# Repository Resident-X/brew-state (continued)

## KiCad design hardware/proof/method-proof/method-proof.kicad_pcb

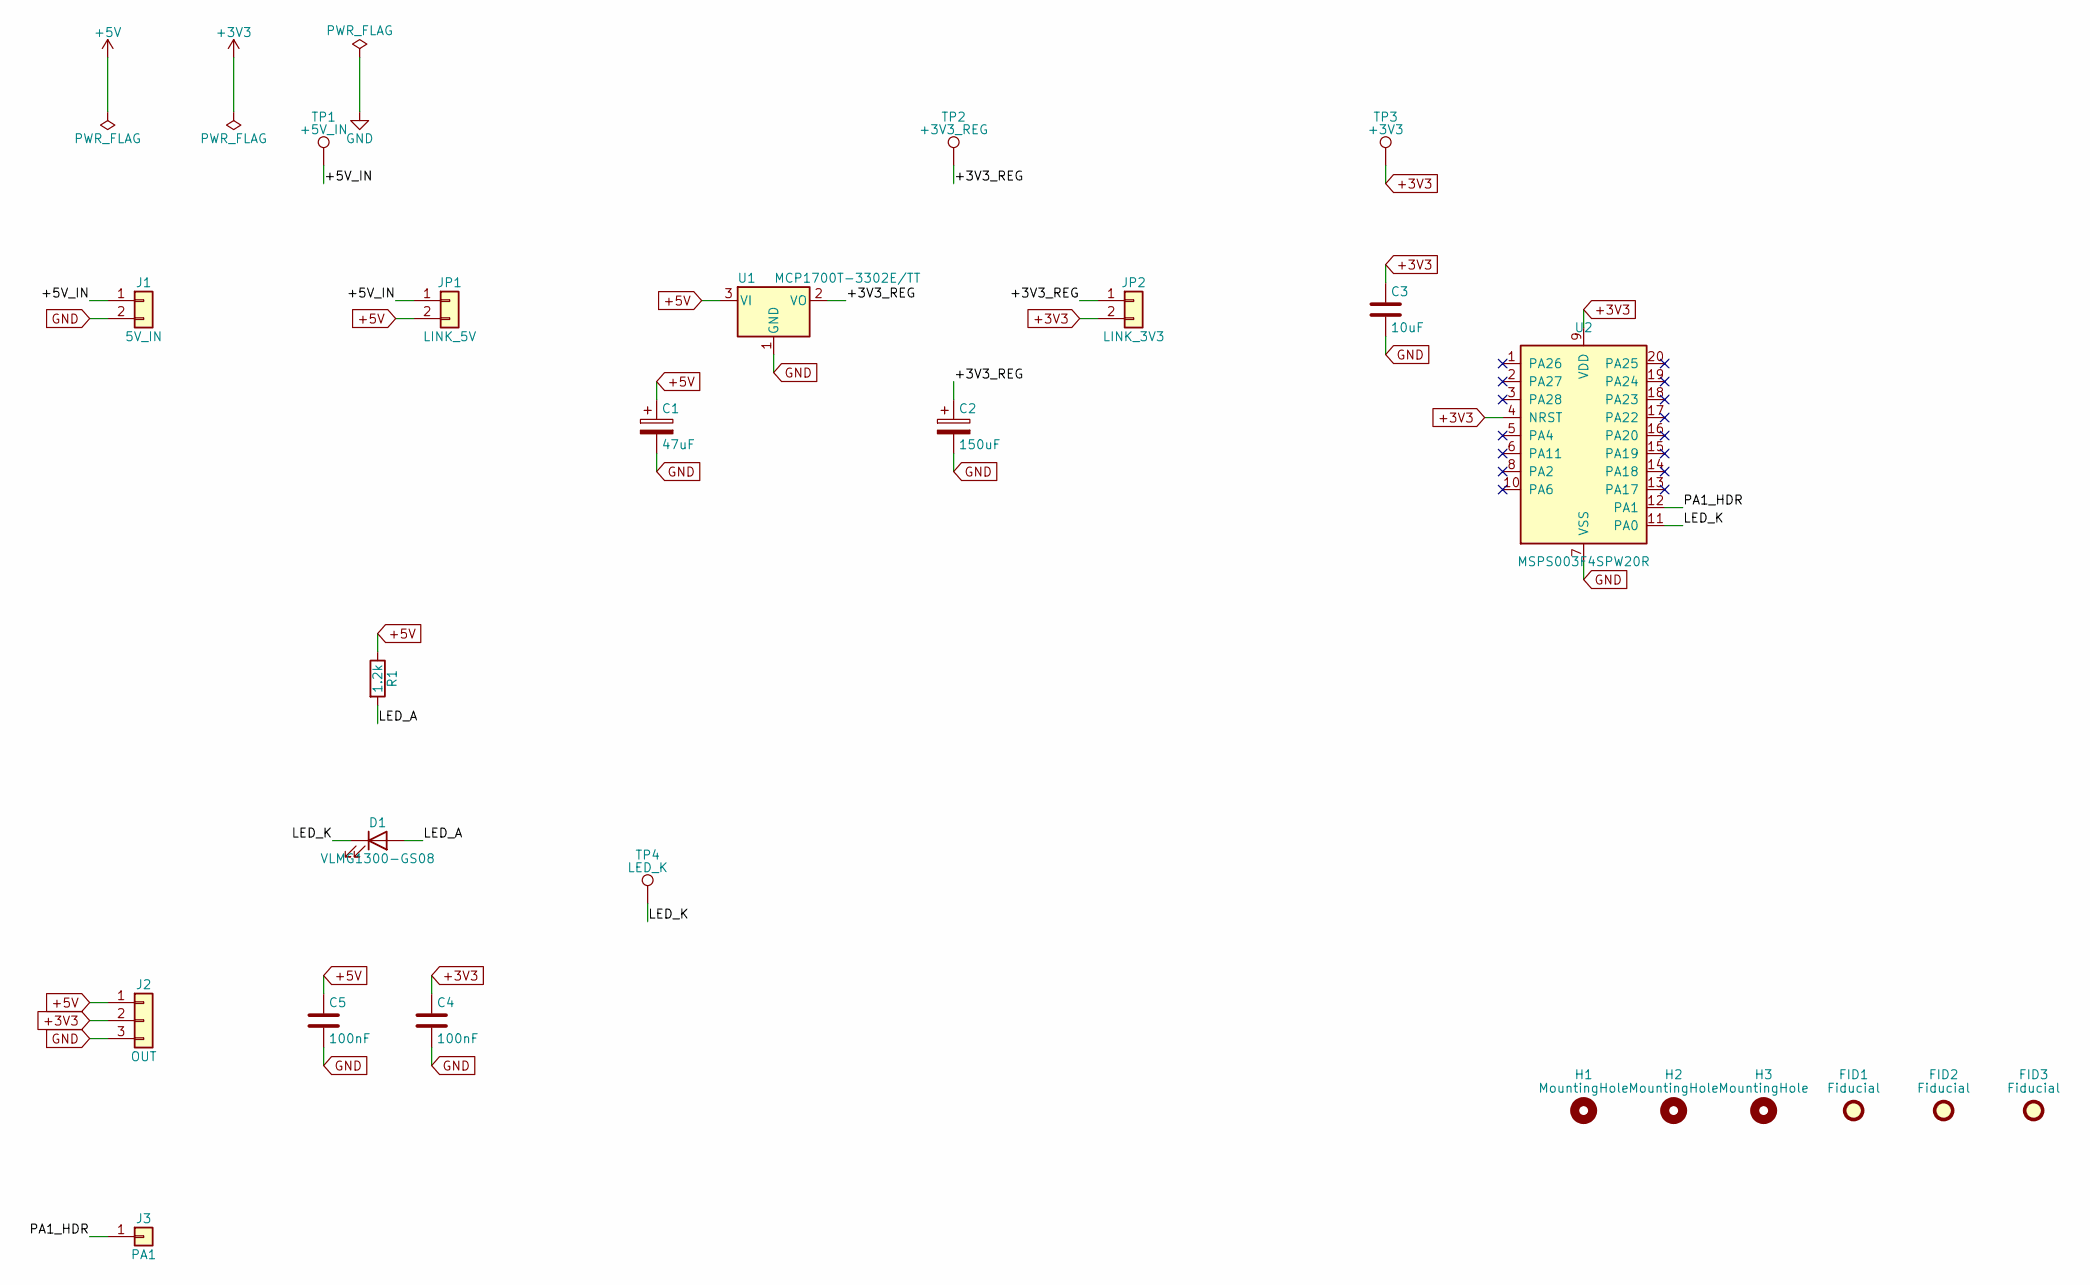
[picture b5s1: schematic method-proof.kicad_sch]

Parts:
C1: 47uF; CP_EIA-3528-21_Kemet-B; Rating 10V; MPN T520B476M010ATE035; LCSC C9100008
C2: 150uF; CP_EIA-3528-21_Kemet-B; Rating 6.3V; MPN T520B157M006ATE025; LCSC C9100014
C3: 10uF; C_0805_2012Metric; Rating 10V; MPN C0805C106K8RACTU; LCSC C9100009
C4, C5: 100nF; C_0603_1608Metric; Rating 16V; MPN C0603C104K4RACTU; LCSC C9100015
D1: VLMG1300-GS08; LED_0603_1608Metric; MPN VLMG1300-GS08; LCSC C9100011
FID1, FID2, FID3: Fiducial; Fiducial_1mm_Mask2mm; LCSC C9100016
H1, H2, H3: MountingHole; MountingHole_2.2mm_M2; LCSC C9100013
J1: 5V_IN; JST_XH_B2B-XH-A_1x02_P2.50mm_Vertical; Rating 3A; MPN B2B-XH-A(LF)(SN); LCSC C9100001
J2: OUT; JST_XH_B3B-XH-A_1x03_P2.50mm_Vertical; Rating 3A; MPN B3B-XH-A(LF)(SN); LCSC C9100002
J3: PA1; PinHeader_1x01_P2.54mm_Vertical; MPN TSW-101-07-T-S; LCSC C9100003
JP1: LINK_5V; PinHeader_1x02_P2.54mm_Vertical; MPN TSW-102-07-T-S; LCSC C9100004
JP2: LINK_3V3; PinHeader_1x02_P2.54mm_Vertical; MPN TSW-102-07-T-S; LCSC C9100005
R1: 1.2k; R_0603_1608Metric; Rating 0.1W; MPN CRCW06031K20FKEA; LCSC C9100010
TP1: +5V_IN; TestPoint_Pad_D1.0mm; LCSC C9100012
TP2: +3V3_REG; TestPoint_Pad_D1.0mm; LCSC C9100012
TP3: +3V3; TestPoint_Pad_D1.0mm; LCSC C9100012
TP4: LED_K; TestPoint_Pad_D1.0mm; LCSC C9100012
U1: MCP1700T-3302E/TT; SOT-23; MPN MCP1700T-3302E/TT; LCSC C9100006
U2: MSPS003F4SPW20R; TSSOP-20_4.4x6.5mm_P0.65mm; MPN MSPS003F4SPW20R; LCSC C9100007

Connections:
+3V3: C3.1, C4.1, J2.2, JP2.2, TP3.1 (1_1), U2.4 (NRST), U2.9 (VDD)
+5V: C1.1, C5.1, J2.1, JP1.2, R1.1, U1.3 (VI)
/+3V3_REG: C2.1, JP2.1, TP2.1 (1_1), U1.2 (VO)
/+5V_IN: J1.1, JP1.1, TP1.1 (1_1)
/LED_A: D1.2 (A), R1.2
/LED_K: D1.1 (K), TP4.1 (1_1), U2.11 (PA0)
/PA1_HDR: J3.1 (Pin_1_1), U2.12 (PA1)
GND: C1.2, C2.2, C3.2, C4.2, C5.2, J1.2, J2.3, U1.1 (GND), U2.7 (VSS)

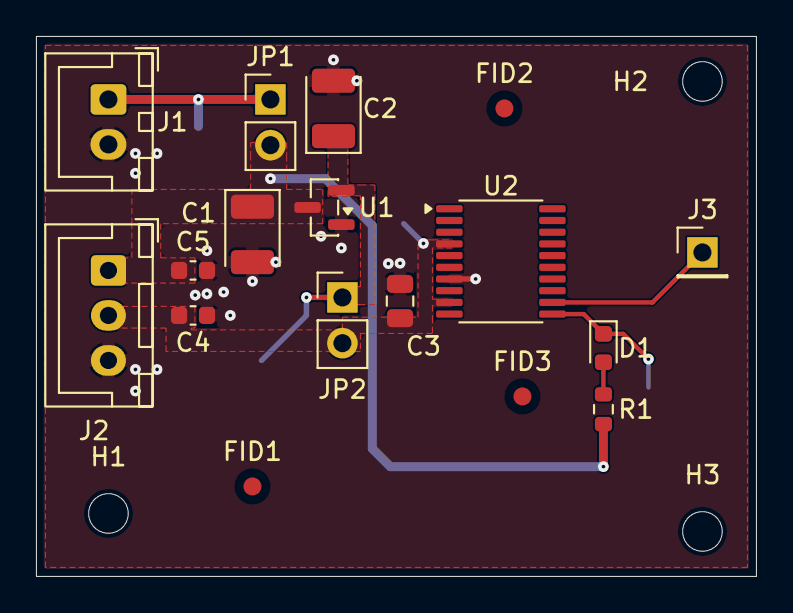
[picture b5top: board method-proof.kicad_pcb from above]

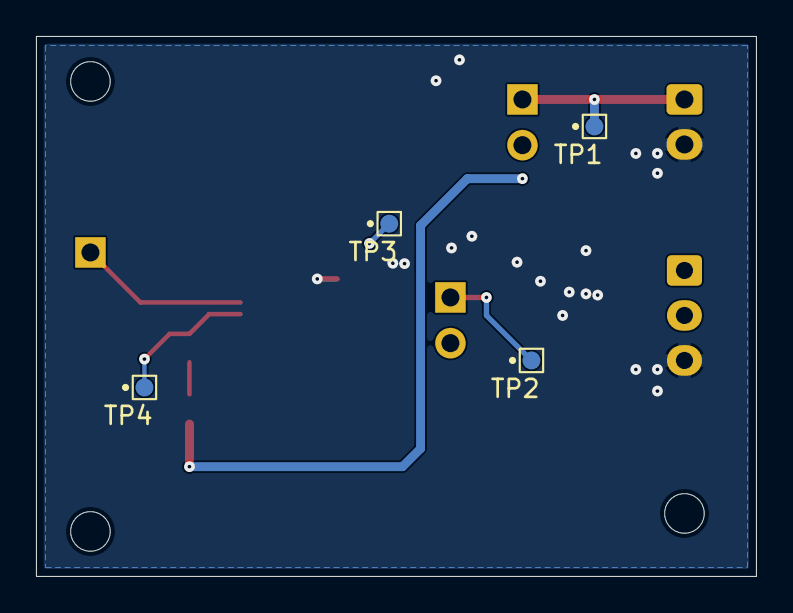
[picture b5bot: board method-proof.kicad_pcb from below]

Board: 4 copper layers, 40.0 x 30.0 mm, 24 parts (4 on the bottom side), 8 nets.

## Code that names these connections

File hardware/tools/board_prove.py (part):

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

def neutral_domain(extra: str, highest: str = "353.5533906"):
    """The mains neutral domain of the pin-limit record given `highest` as its figure and `extra` lines of keys."""
    return pin_limits(NEUTRAL_RAIL, f"    rail: MAINS_N\n    highest_voltage_v: {highest}\n{extra}")


def divider_over_its_rating(seed: Seed) -> None:
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
def riding_domain_on_a_host_below_the_floor(seed: Seed) -> None:
    """The line domain stated at 100 V and the neutral riding on it at half, which the record's derivation allows."""
    pin_limits(LINE_RAIL, "    rail: MAINS_L\n    highest_voltage_v: 100\n")(seed)
    neutral_domain("    rides_on: mains_line\n    fraction: 0.5\n", "50")(seed)


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

def mains_flag_on_lv_b(seed: Seed) -> None:
    """A schematic net class directive putting /LV_B, R2 pin 2's net, in Mains."""
    Q = sexpr.Quoted
    flag = ["netclass_flag", Q(""), ["length", "2.54"], ["shape", "round"], ["at", "45.72", "78.74", "0"],
            ["effects", ["font", ["size", "1.27", "1.27"]], ["justify", "left", "bottom"]],
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            if item[1] == "LV_B" and at[1:3] == ["63.5", "81.28"]:
                tree.remove(item)
                return
        raise AssertionError("the proof schematic has no LV_B label on R2 pin 2")
    seed.schematic(edit)


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

def pour_short_of_pad(seed: Seed) -> None:
    """/LV_A looping the long way round and ending 2.5 mm short of R2's pad 1, inside a pour of its net over the pad,
    which once left the pad out of the route-length rule's tree and the net unmeasured."""
    reroute("/LV_A", (LV_A_ENDS,), [(40, 10), (40, 6), (41, 5), (44, 5), (45, 6), (45, 7.5)])(seed)
    Q = sexpr.Quoted
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
def via_in_decoupling_path(seed: Seed) -> None:
    """U1's two pads typed as power inputs, a capacitor C9 across them 6 mm below U1, and a /LV_A via between C9's /LV_A pad
    and U1's /LV_A pin."""
    Q = sexpr.Quoted
    thru = ("thru_hole", ["*.Cu", "*.Mask"])
    part = small_part("C9", 43, 16, "0b0e5c1a-0000-4000-8000-000000000d00", ("1", *thru, "/LV_A", 0, 0, 1.2),
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def declared_record(first: str, second: str):
    head = "synthetic: true\ncontroller: none\nchannels:\n"
    entry = "  - channel: {label}\n    net: {net}\n    connector: J2\n    connector_pin: {pin}\n{extra}"
    return lambda seed: seed.write("pin-allocation.yaml", head + entry.format(label="lv_a", net="LV_A", pin=1, extra=first)
                                   + (entry.format(label="lv_b", net="LV_B", pin=2, extra=second) if second is not None else ""))


#: Where the far channel fault places its copy: a machine folder, which no proof design sits in, holding the copy alone.
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     "down to 0.9 mm, and the layout leaves 0.84 mm",
     both(TERMINAL_SHORTFALL, NET_PAIR_BANDS, exceptions(net_pair_entry("clearance", ("/MAINS_L",), 125, 0.9, ("/MAINS_N",))))),
    # Connectivity
    ("a channel's net moved to the other controller pin", "connectivity: a net must reach the controller pin its channel names", "connectivity", "net /LV_A reaches controller pin PA1, where the record names controller pin PA0", swap_labels(("LV_A", "96.52 76.2"), ("LV_B", "96.52 78.74"))),
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    ("a channel on the wrong connector", "connectivity: a net must reach the connector its channel names", "connectivity", "net /LV_A reaches connector pin J3 pin 1, where the record names connector pin J2 pin 1", rename_reference("J2", "J3")),
    ("a listed channel removed from the design", "connectivity: a channel the record lists must be in the design", "connectivity", "the record lists net LV_B, which the design does not have", drop_net_labels("LV_B")),
    ("a channel on pins the record omits", "connectivity: a net on a pin the record omits fails", "connectivity", "which the record does not list", pin_record("  - channel: lv_b\n    net: LV_B\n    controller_pin: PA1\n    connector: J2\n    connector_pin: 2\n", "")),
    ("a pin allocation record that does not exist", "pin allocation: a design with no record fails", "pin_allocation", "there is no pin-allocation.yaml", remove("pin-allocation.yaml")),
    ("a pin allocation record that cannot be parsed", "pin allocation: the record is readable", "pin_allocation", "cannot be parsed", pin_record("channels:\n", "channels: [unclosed\n")),
    ("a pin allocation record giving a key twice", "pin allocation: the record is read only in its one form", "pin_allocation", "gives the key 'net' more than once", pin_record("    net: LV_A\n", "    net: LV_A\n    net: LV_B\n")),
    ("a pin allocation record lacking the channels", "pin allocation: a record without channels fails", "pin_allocation", "the record lacks channels", pin_record("channels:\n", "chanels:\n")),
    ("a pin allocation record listing no channel", "pin allocation: an empty record cannot pass a design", "pin_allocation", "lists no channel", lambda seed: seed.write("pin-allocation.yaml", "synthetic: true\nchannels: []\n")),
    ("a pin allocation entry lacking its controller pin", "pin allocation: a record missing a required key fails", "pin_allocation", "the entry lacks controller_pin", pin_record("    controller_pin: PA0\n", "")),
    ("a pin allocation entry naming a connector without its pin", "pin allocation: a record missing a required key fails", "pin_allocation", "gives only one of connector and connector_pin", pin_record("    connector_pin: 1\n", "")),
    ("a synthetic pin allocation record applied to a design not marked not for manufacture", "pin allocation: a synthetic record cannot pass an orderable board", "pin_allocation", "marked synthetic", variables(lambda v: v.pop("NOT_FOR_MANUFACTURE"))),
    # A pin allocation record that declares no controller
    ("a controller placed under a no-controller declaration", "no-controller declaration: a design that places a controller fails, naming the part", "controller_part",
     "declares controller: none, but the design places U1, a part with port-named pins", declared_record("    rail: signal_a\n", "    rail: signal_b\n")),
    ("a controller pin listed under a no-controller declaration", "no-controller declaration: an entry carries no controller pin", "pin_allocation",
     "the record declares controller: none, so the entry carries no controller_pin", declared_record("    rail: signal_a\n    controller_pin: PA0\n", "    rail: signal_b\n")),
    ("a no-controller entry naming neither a far channel nor a rail", "no-controller declaration: an entry names exactly one of far_channel and rail", "pin_allocation",
     "the entry carries neither far_channel nor rail", declared_record("", "    rail: signal_b\n")),
    ("a no-controller entry naming both a far channel and a rail", "no-controller declaration: an entry names exactly one of far_channel and rail", "pin_allocation",
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    ("a far channel that no other design's record lists", "no-controller declaration: a far channel must be listed by another design's record in the machine folder", "pin_allocation",
     "names far channel lv_a, which no other design's record in the machine folder lists", lambda seed: declared_record("    far_channel: lv_a\n", "    rail: signal_b\n")(seed), MACHINE_TARGET),
    ("a pin of a listed connector that a no-controller record omits", "no-controller declaration: a net on a pin of a listed connector must be listed", "connectivity",
     "net /LV_B is on connector pin J2 pin 2, which the record does not list", declared_record("    rail: signal_a\n", None)),
    # Controller part
    ("a controller whose catalogue number differs from the controller part record", "controller part: a controller other than the selected part fails", "controller_part", "the controller U1 has the catalogue number C9000005, where the controller part record names C9000099",
     lambda seed: seed.replace("controller-part.yaml", 'lcsc: "C9000005"', 'lcsc: "C9000099"')),
    ("a controller with no LCSC field", "controller part: a controller whose catalogue number is absent fails", "controller_part", "the controller U1 has no LCSC field", drop_field("U1", "LCSC")),
    ("a pin allocation entry naming a pin the controller part record omits", "controller part: a channel on a pin the selected part does not have fails", "controller_part", "channel lv_b names controller pin PA1, which the selected SYNTHETIC-CTRL does not have",
     lambda seed: seed.replace("controller-part.yaml", "  - PA1\n", "")),
    ("a controller part record that does not exist", "controller part: a design placing a controller with no record fails", "controller_record", "there is no controller-part.yaml", remove("controller-part.yaml")),
    ("a controller part record that cannot be parsed", "controller part: the record is readable", "controller_record", "cannot be parsed", lambda seed: seed.replace("controller-part.yaml", "pins:\n", "pins: [unclosed\n")),
    ("a controller part record lacking its catalogue number", "controller part: a record missing a required key fails", "controller_record", "lacks lcsc", lambda seed: seed.replace("controller-part.yaml", 'lcsc: "C9000005"\n', "")),
    ("a controller part record holding a key no decision names", "controller part: the record is read only in its one form", "controller_record", "holds the key 'package'", lambda seed: seed.replace("controller-part.yaml", "synthetic: true\n", "synthetic: true\npackage: LQFP144\n")),
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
